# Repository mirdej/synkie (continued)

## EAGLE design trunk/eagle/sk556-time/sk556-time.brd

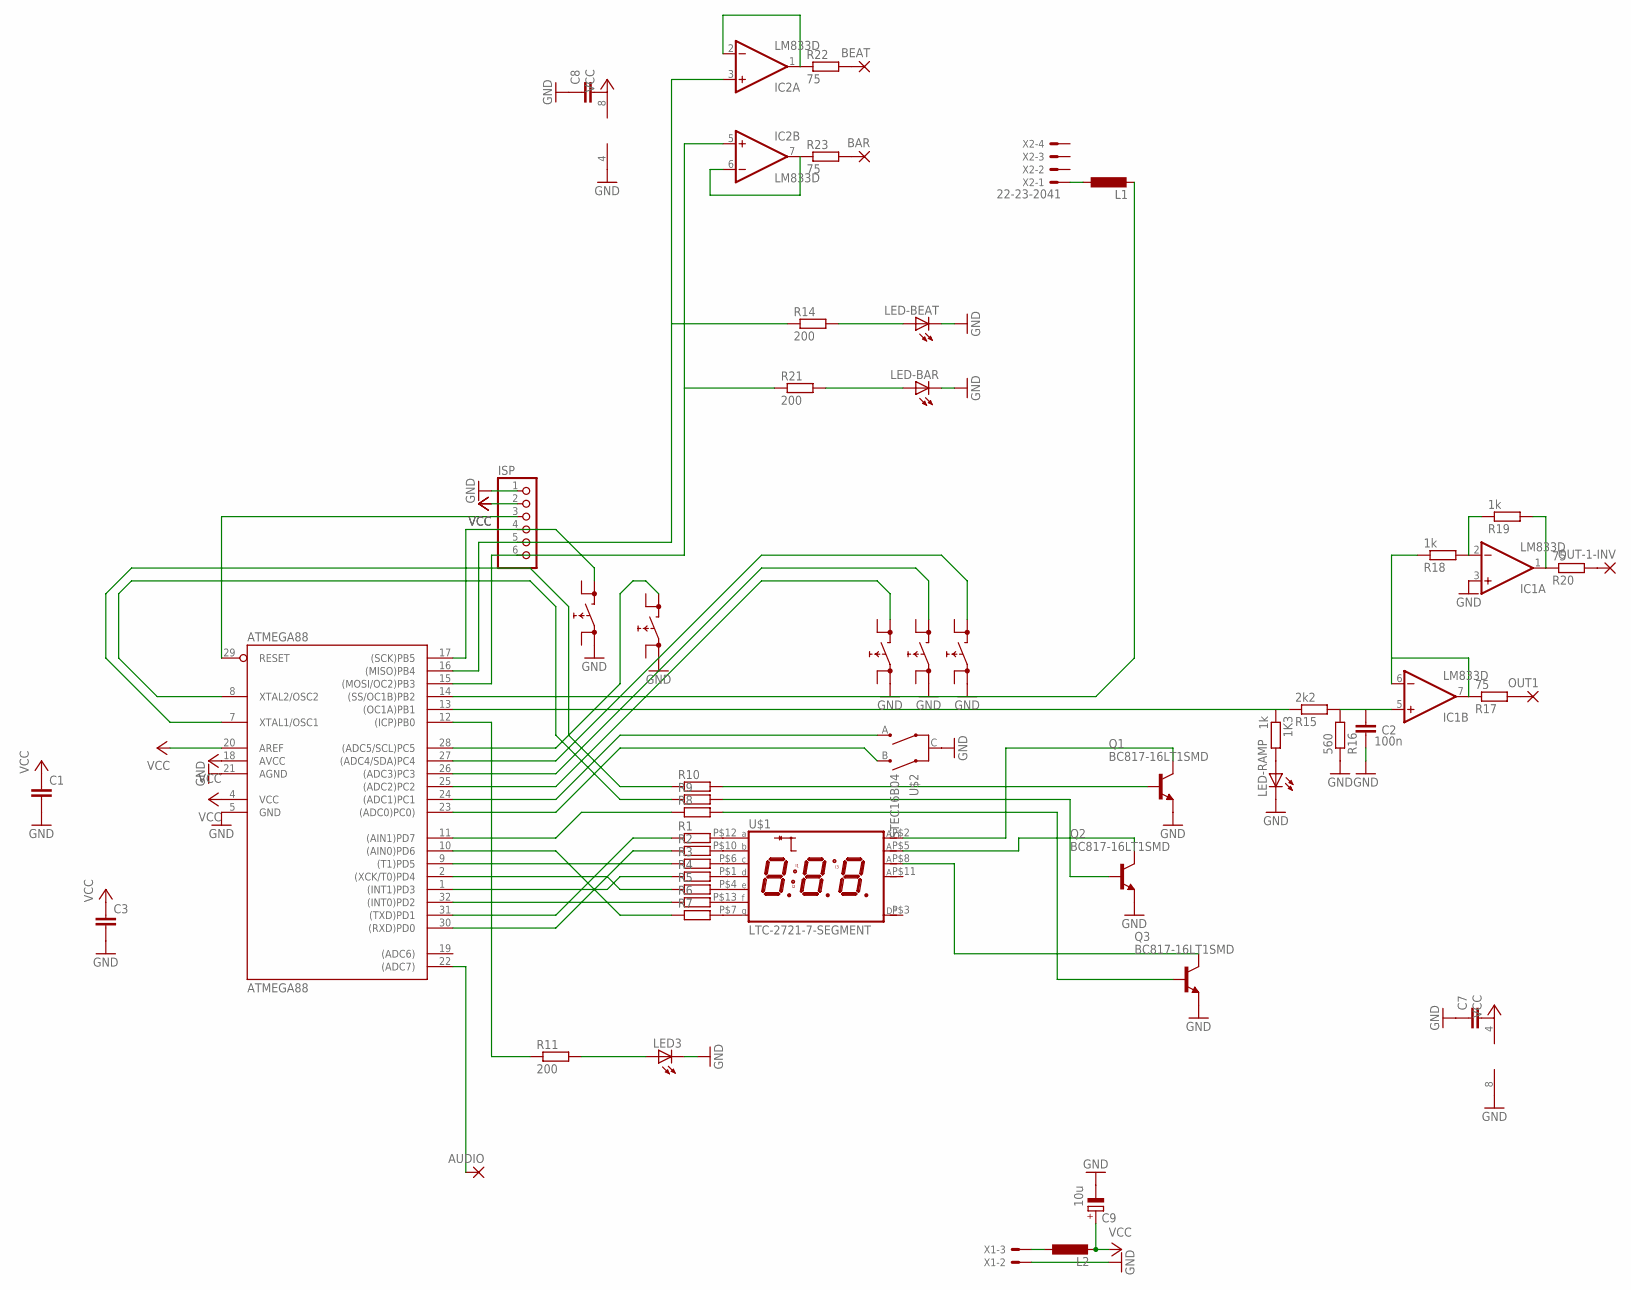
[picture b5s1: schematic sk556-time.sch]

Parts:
1K3: 1k; R1206
ATMEGA88: ATMEGA88; TQFP32-08
AUDIO: 3,17/1,1
BAR: 3,17/1,1
BEAT: 3,17/1,1
C1, C3, C7: C-EUC0603; C0603
C2: 100n; C0805
C8: C-EUC1206; C1206
C9: 10u; CT3528
IC1, IC2: LM833D; SO08
ISP: PINHD-1X6; 1X06
L1, L2: L-EUL5038P; L5038P
LED3: LEDCHIPLED_1206; CHIPLED_1206
LED-BAR: LEDCHIPLED_1206; CHIPLED_1206
LED-BEAT: LEDCHIPLED_1206; CHIPLED_1206
LED-RAMP: LEDCHIPLED_1206; CHIPLED_1206
LEFT: PRINTTASTER_SMD; SMD_SWITCH
LOOPER: PRINTTASTER_SMD; SMD_SWITCH
MIDDLE: PRINTTASTER_SMD; SMD_SWITCH
OUT1: 3,17/1,1
OUT-1-INV: 3,17/1,1
Q1, Q2, Q3: BC817-16LT1SMD; SOT23-BEC
R1, R2, R3, R4, R5, R6, R7, R8, R9, R10: R-EU_R1206; R1206
R11, R14, R21: 200; R1206
R15: 2k2; R1206
R16: 560; R1206
R17, R20, R22, R23: 75; R1206
R18, R19: 1k; R1206
RIGHT: PRINTTASTER_SMD; SMD_SWITCH
TAP: PRINTTASTER_SMD; SMD_SWITCH
U$1: LTC-2721-7-SEGMENT; LTC-2721
U$2: STEC16B04
X1: 22-23-2031
X2: 22-23-2041

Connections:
MISO: ATMEGA88.16 ((MISO)PB4), IC2.3 (+IN), ISP.5, R14.1
MOSI: ATMEGA88.15 ((MOSI/OC2)PB3), IC2.5 (+IN), ISP.6, R21.1
unnamed: ATMEGA88.30 ((RXD)PD0), R2.1
unnamed: ATMEGA88.31 ((TXD)PD1), R1.1
unnamed: ATMEGA88.32 ((INT0)PD2), R6.1
unnamed: ATMEGA88.1 ((INT1)PD3), R4.1
unnamed: ATMEGA88.2 ((XCK/T0)PD4), R5.1
unnamed: ATMEGA88.8 (XTAL2/OSC2), R9.1
unnamed: ATMEGA88.7 (XTAL1/OSC1), R10.1
unnamed: ATMEGA88.11 ((AIN1)PD7), R8.1
unnamed: ATMEGA88.9 ((T1)PD5), R3.1
unnamed: R1.2, U$1.P$12 (A)
unnamed: R2.2, U$1.P$10 (B)
unnamed: R3.2, U$1.P$6 (C)
unnamed: R4.2, U$1.P$1 (D)
unnamed: R5.2, U$1.P$4 (E)
unnamed: R6.2, U$1.P$13 (F)
unnamed: R7.2, U$1.P$7 (G)
unnamed: ATMEGA88.29 (RESET), ISP.3
unnamed: ATMEGA88.22 ((ADC7)), AUDIO.1
unnamed 20: ATMEGA88.14 ((SS/OC1B)PB2), L1.2; also elsewhere on the board
unnamed 21: L1.1, X2.1; also elsewhere on the board
unnamed: ATMEGA88.10 ((AIN0)PD6), R7.1
unnamed: ATMEGA88.23 ((ADC0)PC0)), U$2.B
unnamed: ATMEGA88.24 ((ADC1)PC1), U$2.A
unnamed: Q1.B, R10.2
unnamed: Q2.B, R9.2
unnamed: Q3.B, R8.2
unnamed: Q1.C, U$1.P$2 (D1)
unnamed: Q2.C, U$1.P$5 (D2)
unnamed: Q3.C, U$1.P$8 (D3)
unnamed: ATMEGA88.25 ((ADC2)PC2), RIGHT.BB (1)
unnamed: ATMEGA88.26 ((ADC3)PC3), MIDDLE.BB (1)
unnamed: ATMEGA88.27 ((ADC4/SDA)PC4), LEFT.BB (1)
unnamed: LED-BEAT.A, R14.2
unnamed: ATMEGA88.28 ((ADC5/SCL)PC5), LOOPER.BB (1)
unnamed: ATMEGA88.12 ((ICP)PB0), R11.1
unnamed: LED-BAR.A, R21.2
unnamed: IC2.1 (OUT), IC2.2 (-IN), R22.1
unnamed: 1K3.1, ATMEGA88.13 ((OC1A)PB1), R15.1
unnamed: C2.1, IC1.5 (+IN), R15.2, R16.2
unnamed: IC1.6 (-IN), IC1.7 (OUT), R17.1, R18.1
unnamed: 1K3.2, LED-RAMP.A
unnamed: IC1.2 (-IN), R18.2, R19.1
unnamed: OUT-1-INV.1, R20.2
unnamed: OUT1.1, R17.2
unnamed: BEAT.1, R22.2
unnamed: IC2.6 (-IN), IC2.7 (OUT), R23.1
unnamed: BAR.1, R23.2
unnamed: L2.1, X1.3
unnamed: IC1.1 (OUT), R19.2, R20.1
unnamed: LED3.A, R11.2
SCK: ATMEGA88.17 ((SCK)PB5), ISP.4, TAP.BB (1)

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
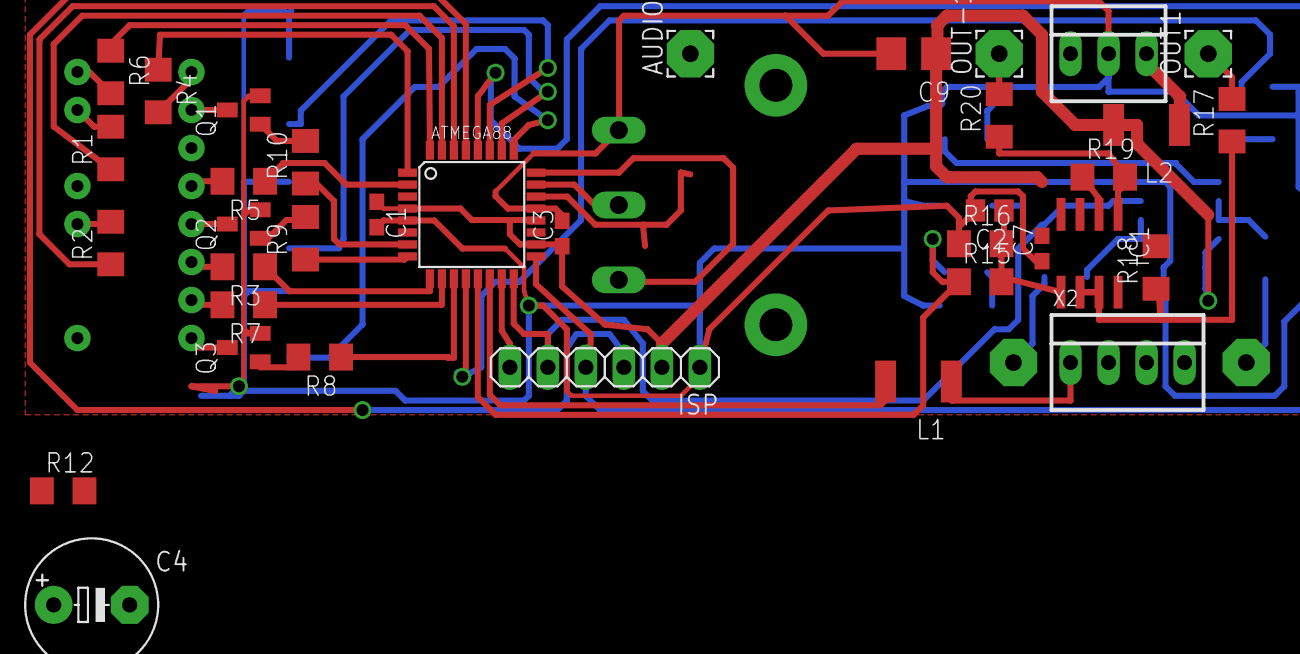
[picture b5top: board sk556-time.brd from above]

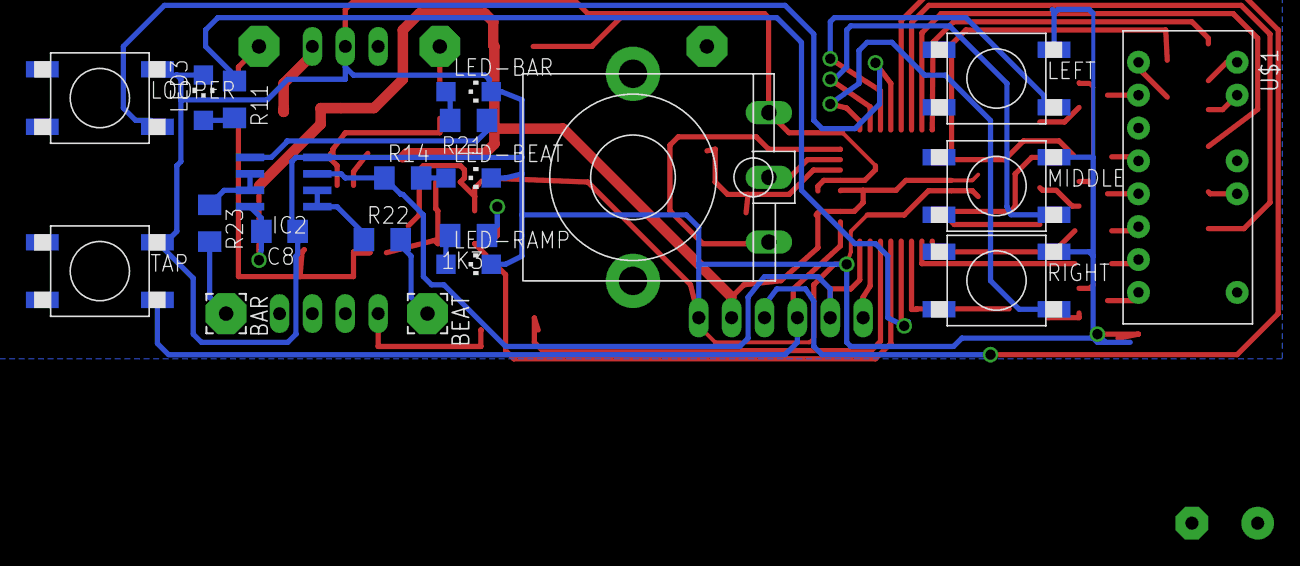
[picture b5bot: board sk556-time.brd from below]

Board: 2 copper layers, 57 parts (21 on the bottom side), 56 nets.

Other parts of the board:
C4: E5-8,5
R12: 100; R1206

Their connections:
unnamed 20: C4.+, R12.2; also elsewhere on the board
unnamed 21: R12.1; also elsewhere on the board

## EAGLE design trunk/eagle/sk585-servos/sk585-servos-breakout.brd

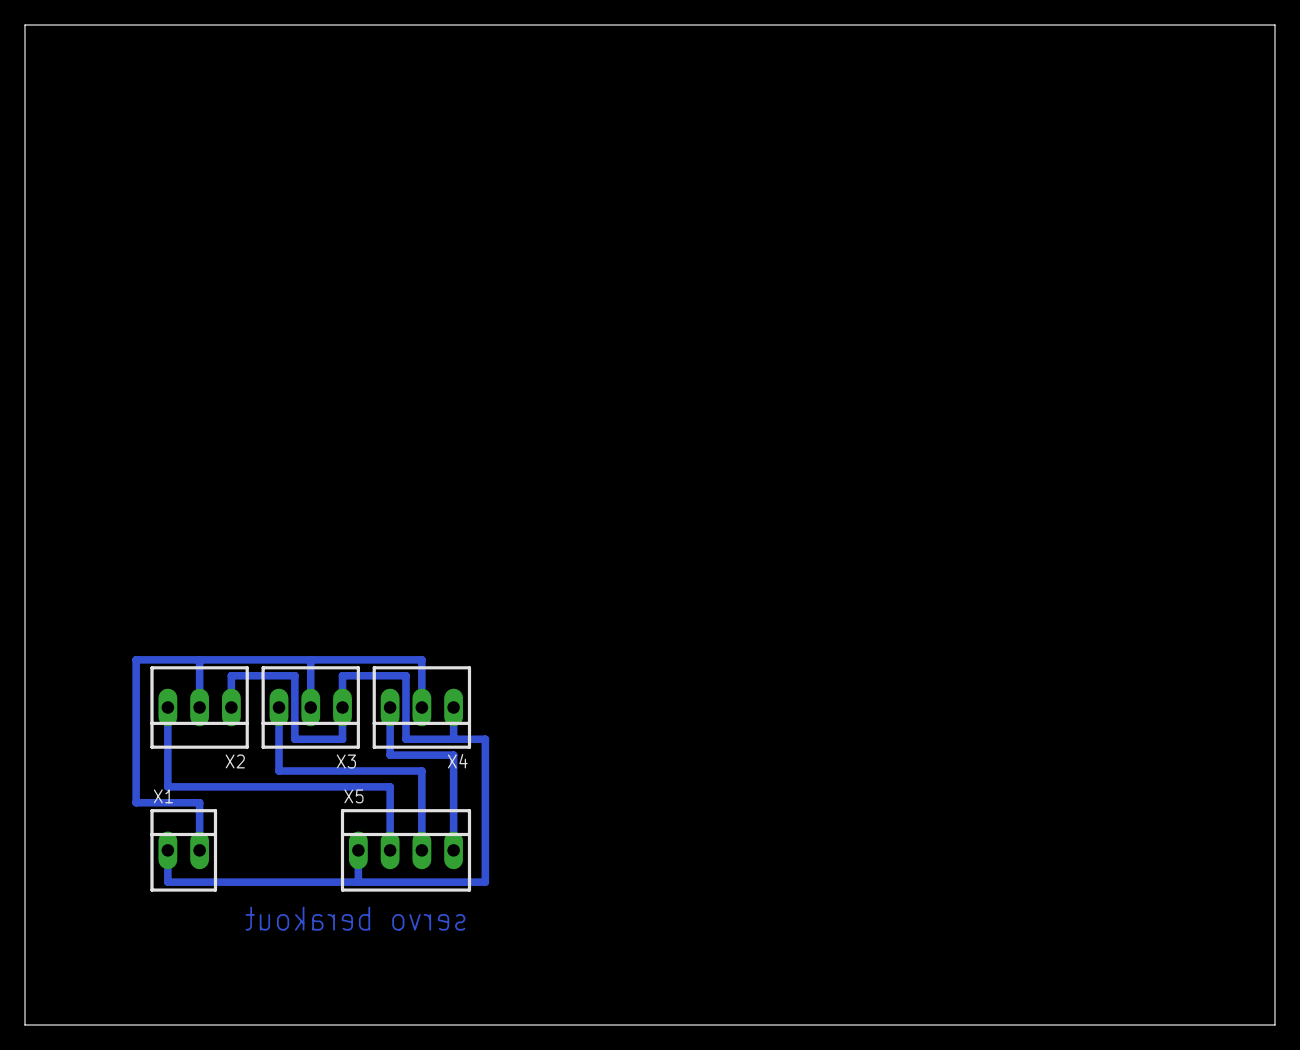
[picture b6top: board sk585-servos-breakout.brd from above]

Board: 2 copper layers, 100.0 x 80.0 mm, 5 parts (0 on the bottom side), 5 nets.

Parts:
X1: 22-23-2021
X2, X3, X4: 22-23-2031
X5: 22-23-2041

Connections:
GND: X1.1, X2.1, X3.1, X4.1, X5.1
unnamed: X4.3, X5.4
unnamed: X3.3, X5.3
unnamed: X2.3, X5.2
VCC: X1.2, X2.2, X3.2, X4.2

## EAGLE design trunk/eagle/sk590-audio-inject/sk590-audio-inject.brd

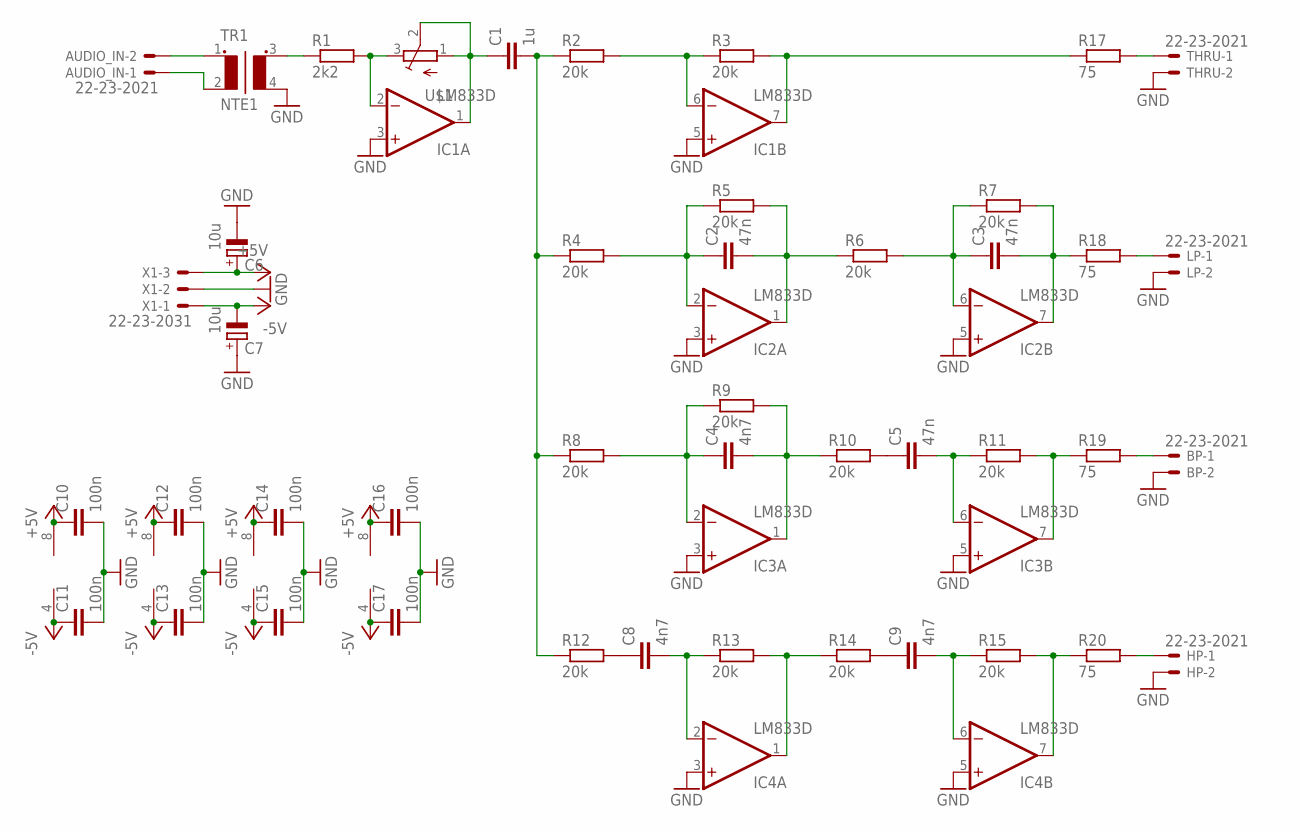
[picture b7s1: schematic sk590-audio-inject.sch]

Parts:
AUDIO_IN: 22-23-2021
BP: 22-23-2021
C1: 1u; C1206
C2, C3, C5: 47n; C1206
C4, C8, C9: 4n7; C1206
C6, C7: 10u; CT3528
C10, C11, C12, C13, C14, C15, C16, C17: 100n; C1206
HP: 22-23-2021
IC1, IC2, IC3, IC4: LM833D; SO08
LP: 22-23-2021
R1: 2k2; R1206
R2, R3, R4, R5, R6, R7, R8, R9, R10, R11, R12, R13, R14, R15: 20k; R1206
R17, R18, R19, R20: 75; R1206
THRU: 22-23-2021
TR1: NTE1; PE-65612
U$1: ALPS_RK09K111_HOHNE-FüSSE; ALPS_RK09K111
X1: 22-23-2031

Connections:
+5V: C6.+, C10.1, C12.1, C14.1, C16.1, IC1.8 (V+), IC2.8 (V+), IC3.8 (V+), IC4.8 (V+), X1.3
-5V: C7.-, C11.1, C13.1, C15.1, C17.1, IC1.4 (V-), IC2.4 (V-), IC3.4 (V-), IC4.4 (V-), X1.1
GND: BP.2, C6.-, C7.+, C10.2, C11.2, C12.2, C13.2, C14.2, C15.2, C16.2, C17.2, HP.2, IC1.3 (+IN), IC1.5 (+IN), IC2.3 (+IN), IC2.5 (+IN), IC3.3 (+IN), IC3.5 (+IN), IC4.3 (+IN), IC4.5 (+IN), LP.2, THRU.2, TR1.4 (S2), X1.2
unnamed: AUDIO_IN.2, TR1.1
unnamed: AUDIO_IN.1, TR1.2
unnamed: R1.1, TR1.3 (S1)
unnamed: IC1.2 (-IN), R1.2, U$1.3 (E)
unnamed: C1.1, IC1.1 (OUT), U$1.1 (S), U$1.2 (W)
unnamed: C1.2, R2.1, R4.1, R8.1, R12.1
unnamed: IC1.6 (-IN), R2.2, R3.1
unnamed: IC1.7 (OUT), R3.2, R17.1
unnamed: C2.1, IC2.2 (-IN), R4.2, R5.1
unnamed: C2.2, IC2.1 (OUT), R5.2, R6.1
unnamed: C3.1, IC2.6 (-IN), R6.2, R7.1
unnamed: C3.2, IC2.7 (OUT), R7.2, R18.1
unnamed: C5.1, R10.2
unnamed: C8.1, R12.2
unnamed: C4.1, IC3.2 (-IN), R8.2, R9.1
unnamed: C8.2, IC4.2 (-IN), R13.1
unnamed: IC4.1 (OUT), R13.2, R14.1
unnamed: C4.2, IC3.1 (OUT), R9.2, R10.1
unnamed: C5.2, IC3.6 (-IN), R11.1
unnamed: IC3.7 (OUT), R11.2, R19.1
unnamed: C9.1, R14.2
unnamed: C9.2, IC4.6 (-IN), R15.1
unnamed: IC4.7 (OUT), R15.2, R20.1
unnamed: R17.2, THRU.1
unnamed: LP.1, R18.2
unnamed: BP.1, R19.2
unnamed: HP.1, R20.2

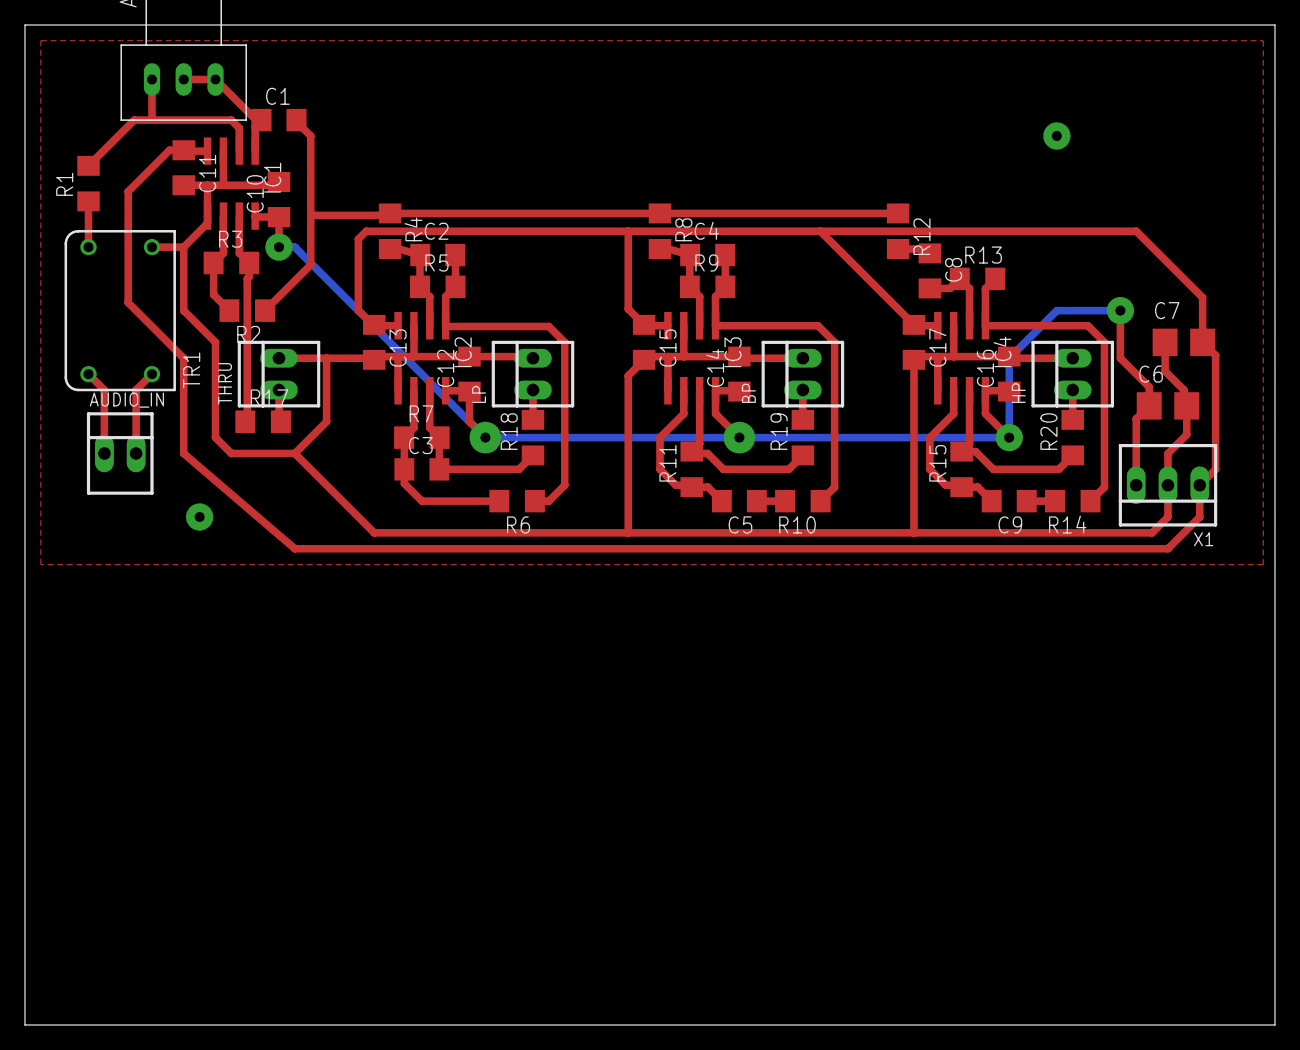
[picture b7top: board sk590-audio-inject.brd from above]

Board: 2 copper layers, 100.0 x 80.0 mm, 48 parts (0 on the bottom side), 30 nets.
